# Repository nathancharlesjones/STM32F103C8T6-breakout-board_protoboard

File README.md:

# STM32F103C8T6 Breakout Board - Protoboard

Breakout board for the venerable STM32F103C8T6 (a.k.a. the "Blue Pill") intended to be assembled by JLC PCB. Includes a small prototyping area which is intended to resemble the layout of a standard half-sized breadboard. All of the pads on the breadboard are connected through just a single trace on the bottom of the PCB. This allows some to be easily cut (using a hobby knife or small cutting tool such as a Dremel), which could allow for a slightly denser layout of some circuits.

For more information about this PCB and how to order one, visit [this Git repository](https://github.com/nathancharlesjones/STM32F103C8T6-breakout-board).

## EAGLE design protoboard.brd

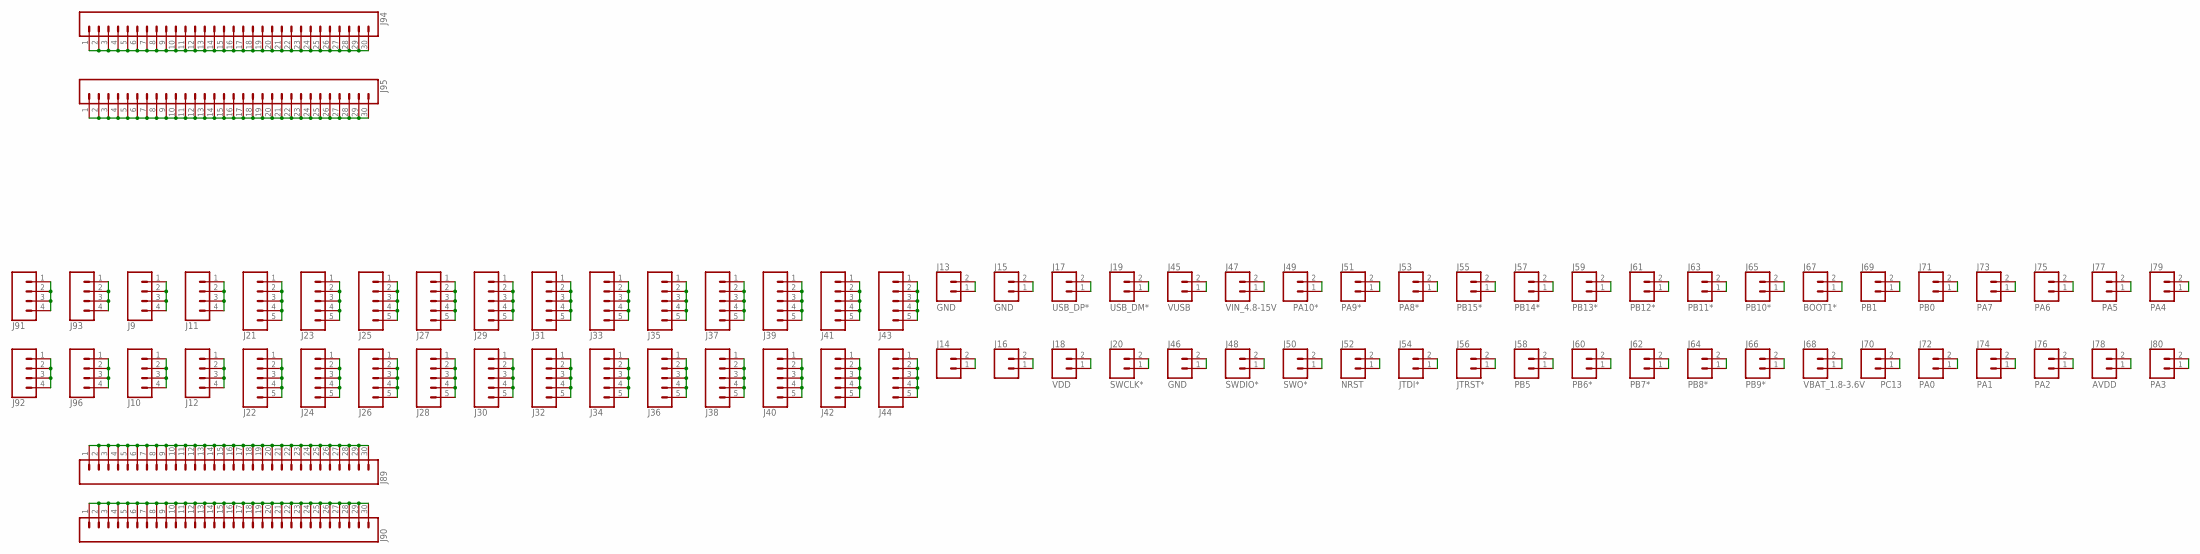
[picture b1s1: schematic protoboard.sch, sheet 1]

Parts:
J9, J10, J11, J12, J91, J92, J93, J96: CONN_041X04_NO_SILK; 1X04_NO_SILK
J13, J14, J15, J16, J17, J18, J19, J20, J45, J46, J47, J48, J49, J50, J51, J52, J53, J54, J55, J56, J57, J58, J59, J60, J61, J62, J63, J64, J65, J66, J67, J68, J69, J70, J71, J72, J73, J74, J75, J76, J77, J78, J79, J80: CONN_021X02_NO_SILK; 1X02_NO_SILK
J21, J22, J23, J24, J25, J26, J27, J28, J29, J30, J31, J32, J33, J34, J35, J36, J37, J38, J39, J40, J41, J42, J43, J44: CONN_05NO_SILK; 1X05_NO_SILK
J89, J90, J94, J95: CONN_30NO_SILK; 1X30_NO_SILK

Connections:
AVDD: J78.1, J78.2; also elsewhere on the board
BOOT1*: J67.1, J67.2; also elsewhere on the board
GND: J13.1, J13.2, J15.1, J15.2, J46.1, J46.2; also elsewhere on the board
JTDI*: J54.1, J54.2; also elsewhere on the board
JTRST*: J56.1, J56.2; also elsewhere on the board
unnamed: J90.1, J90.2, J90.3, J90.4, J90.5, J90.6, J90.7, J90.8, J90.9, J90.10, J90.11, J90.12, J90.13, J90.14, J90.15, J90.16, J90.17, J90.18, J90.19, J90.20, J90.21, J90.22, J90.23, J90.24, J90.25, J90.26, J90.27, J90.28, J90.29, J90.30
unnamed: J89.1, J89.2, J89.3, J89.4, J89.5, J89.6, J89.7, J89.8, J89.9, J89.10, J89.11, J89.12, J89.13, J89.14, J89.15, J89.16, J89.17, J89.18, J89.19, J89.20, J89.21, J89.22, J89.23, J89.24, J89.25, J89.26, J89.27, J89.28, J89.29, J89.30
unnamed: J95.1, J95.2, J95.3, J95.4, J95.5, J95.6, J95.7, J95.8, J95.9, J95.10, J95.11, J95.12, J95.13, J95.14, J95.15, J95.16, J95.17, J95.18, J95.19, J95.20, J95.21, J95.22, J95.23, J95.24, J95.25, J95.26, J95.27, J95.28, J95.29, J95.30
unnamed: J94.1, J94.2, J94.3, J94.4, J94.5, J94.6, J94.7, J94.8, J94.9, J94.10, J94.11, J94.12, J94.13, J94.14, J94.15, J94.16, J94.17, J94.18, J94.19, J94.20, J94.21, J94.22, J94.23, J94.24, J94.25, J94.26, J94.27, J94.28, J94.29, J94.30
unnamed: J92.1, J92.2, J92.3, J92.4
unnamed: J96.1, J96.2, J96.3, J96.4
unnamed: J10.1, J10.2, J10.3, J10.4
unnamed: J12.1, J12.2, J12.3, J12.4
unnamed: J22.1, J22.2, J22.3, J22.4, J22.5
unnamed: J24.1, J24.2, J24.3, J24.4, J24.5
unnamed: J26.1, J26.2, J26.3, J26.4, J26.5
unnamed: J28.1, J28.2, J28.3, J28.4, J28.5
unnamed: J30.1, J30.2, J30.3, J30.4, J30.5
unnamed: J32.1, J32.2, J32.3, J32.4, J32.5
unnamed: J34.1, J34.2, J34.3, J34.4, J34.5
unnamed: J36.1, J36.2, J36.3, J36.4, J36.5
unnamed: J38.1, J38.2, J38.3, J38.4, J38.5
unnamed: J40.1, J40.2, J40.3, J40.4, J40.5
unnamed: J42.1, J42.2, J42.3, J42.4, J42.5
unnamed: J44.1, J44.2, J44.3, J44.4, J44.5
unnamed: J14.1, J14.2
unnamed: J16.1, J16.2
unnamed: J91.1, J91.2, J91.3, J91.4
unnamed: J93.1, J93.2, J93.3, J93.4
unnamed: J9.1, J9.2, J9.3, J9.4
unnamed: J11.1, J11.2, J11.3, J11.4
unnamed: J21.1, J21.2, J21.3, J21.4, J21.5
unnamed: J23.1, J23.2, J23.3, J23.4, J23.5
unnamed: J25.1, J25.2, J25.3, J25.4, J25.5
unnamed: J27.1, J27.2, J27.3, J27.4, J27.5
unnamed: J29.1, J29.2, J29.3, J29.4, J29.5
unnamed: J31.1, J31.2, J31.3, J31.4, J31.5
unnamed: J33.1, J33.2, J33.3, J33.4, J33.5
unnamed: J35.1, J35.2, J35.3, J35.4, J35.5
unnamed: J37.1, J37.2, J37.3, J37.4, J37.5
unnamed: J39.1, J39.2, J39.3, J39.4, J39.5
unnamed: J41.1, J41.2, J41.3, J41.4, J41.5
unnamed: J43.1, J43.2, J43.3, J43.4, J43.5
NRST: J52.1, J52.2; also elsewhere on the board
PA0: J72.1, J72.2; also elsewhere on the board
PA1: J74.1, J74.2; also elsewhere on the board
PA2: J76.1, J76.2; also elsewhere on the board
PA3: J80.1, J80.2; also elsewhere on the board
PA4: J79.1, J79.2; also elsewhere on the board
PA5: J77.1, J77.2; also elsewhere on the board
PA6: J75.1, J75.2; also elsewhere on the board
PA7: J73.1, J73.2; also elsewhere on the board
PA8*: J53.1, J53.2; also elsewhere on the board
PA9*: J51.1, J51.2; also elsewhere on the board
PA10*: J49.1, J49.2; also elsewhere on the board
PB0: J71.1, J71.2; also elsewhere on the board
PB1: J69.1, J69.2; also elsewhere on the board
PB5: J58.1, J58.2; also elsewhere on the board
PB6*: J60.1, J60.2; also elsewhere on the board
PB7*: J62.1, J62.2; also elsewhere on the board
PB8*: J64.1, J64.2; also elsewhere on the board
PB9*: J66.1, J66.2; also elsewhere on the board
PB10*: J65.1, J65.2; also elsewhere on the board
PB11*: J63.1, J63.2; also elsewhere on the board
PB12*: J61.1, J61.2; also elsewhere on the board
PB13*: J59.1, J59.2; also elsewhere on the board
PB14*: J57.1, J57.2; also elsewhere on the board
PB15*: J55.1, J55.2; also elsewhere on the board
PC13: J70.1, J70.2; also elsewhere on the board
SWCLK*: J20.1, J20.2; also elsewhere on the board
SWDIO*: J48.1, J48.2; also elsewhere on the board
SWO*: J50.1, J50.2; also elsewhere on the board
USB_DM*: J19.1, J19.2; also elsewhere on the board
USB_DP*: J17.1, J17.2; also elsewhere on the board
VBAT_1.8-3.6V: J68.1, J68.2; also elsewhere on the board
VDD: J18.1, J18.2; also elsewhere on the board
VIN_4.8-15V: J47.1, J47.2; also elsewhere on the board
VUSB: J45.1, J45.2; also elsewhere on the board

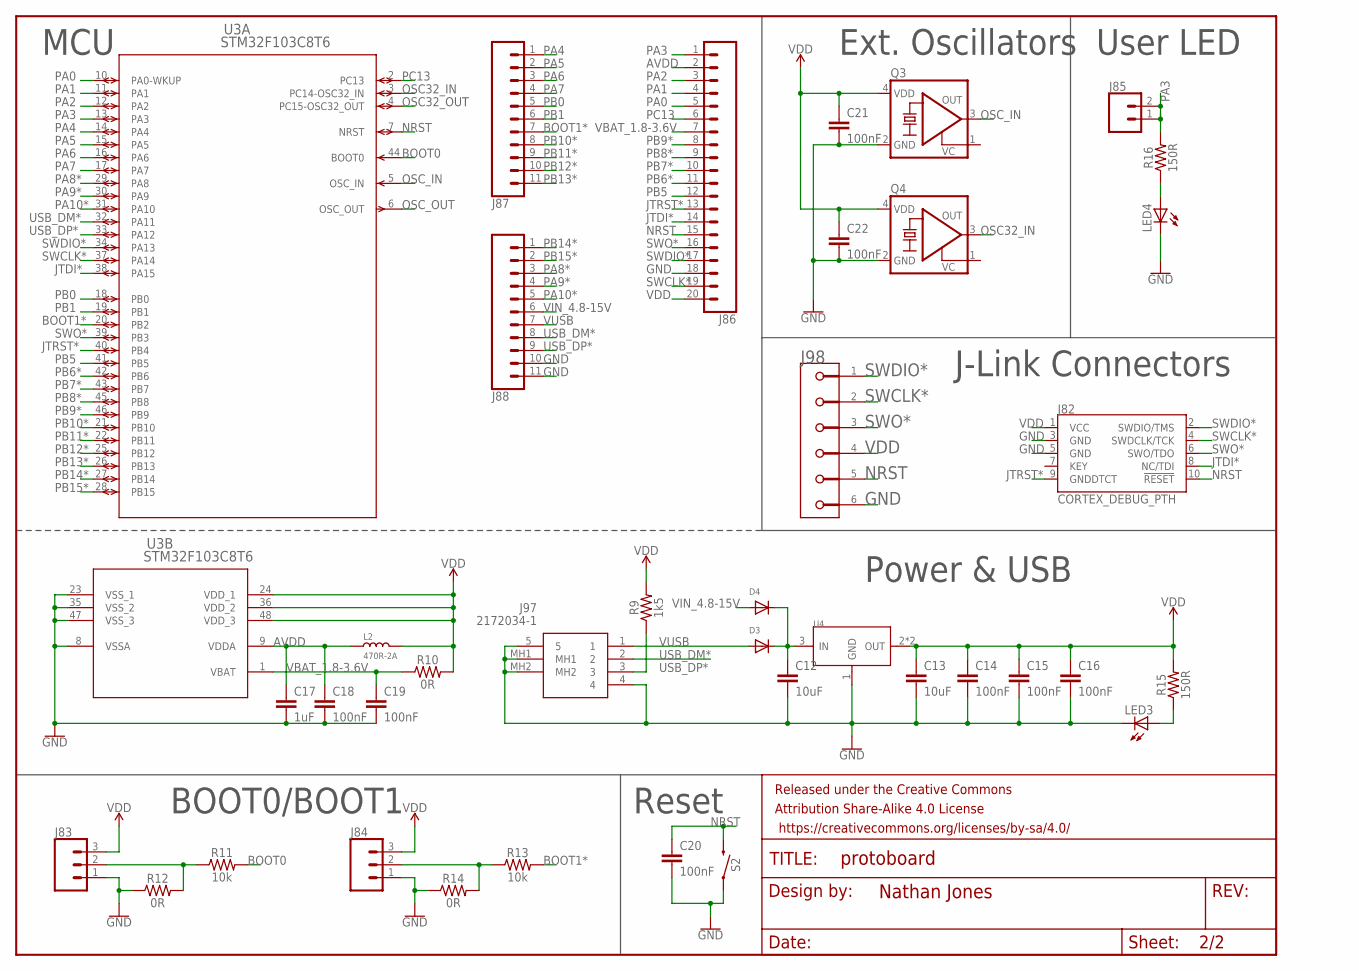
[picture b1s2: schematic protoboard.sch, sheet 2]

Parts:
C12, C13: 10uF; 0402-TIGHT; LCSC_PART C15525
C14, C15, C16, C18, C19, C20, C21, C22: 100nF; 0402-TIGHT; LCSC_PART C1525
C17: 1uF; 0402-TIGHT; LCSC_PART C52923
D3, D4: DIODESOD-123; SOD-123; LCSC_PART C8598
FRAME1: FRAME-LETTERNO_PACKAGE; DUMMY
J82: CORTEX_DEBUG_PTH; 2X5-PTH-1.27MM
J83, J84: CONN_031X03_NO_SILK; 1X03_NO_SILK
J85: CONN_021X02_NO_SILK; 1X02_NO_SILK
J86: CONN_20NOSILK; 1X20_NOSILK
J87, J88: CONN_111X11_NO_SILK; 1X11_NO_SILK
J97: 2172034-1; 21720341
J98: AVX_6-PIN_009159006061916_33MIL-GAP
L2: 470R-2A; L0805; LCSC_PART C1015
LED3: LEDCHIPLED_0603; CHIPLED_0603; LCSC_PART C72041
LED4: LEDCHIPLED_0603; CHIPLED_0603; LCSC_PART C72038
Q3: KXO-VCXO-CMOS_4; 3.2X2.5_KXO-84-TCXO; LCSC_PART C39097
Q4: KXO-VCXO-CMOS_4; 3.2X2.5_KXO-84-TCXO; LCSC_PART C387415
R9: 1k5; 0402; LCSC_PART C25867
R10, R12, R14: 0R; 0402; LCSC_PART C17168
R11, R13: 10k; 0402; LCSC_PART C25744
R15, R16: 150R; 0402; LCSC_PART C25082
S2: MOMENTARY-SWITCH-SPST-SMD-5.2-REDUNDANT; TACTILE_SWITCH_SMD_5.2MM; LCSC_PART C318884
U3: STM32F103C8T6; LQFP48-7X7MM; LCSC_PART C94046
U4: CJT1117-3.3-SOT223; SOT-223; LCSC_PART C6186

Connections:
AVDD: C17.1, C18.1, J86.2, L2.1, U3.9 (VDDA); also elsewhere on the board
BOOT0: R11.2, U3.44 (BOOT0)
BOOT1*: J87.7, R13.2, U3.20 (PB2); also elsewhere on the board
GND: C12.2, C13.2, C14.2, C15.2, C16.2, C17.2, C18.2, C19.2, C20.2, C21.2, C22.2, J82.3 (GND), J82.5 (GND), J83.1, J84.1, J86.18, J88.10, J88.11, J97.4, J97.5, J97.MH1, J97.MH2, J98.6, LED3.C, LED4.C, Q3.2 (GND), Q4.2 (GND), R12.1, R14.1, S2.1, S2.2 (1), U3.8 (VSSA), U3.23 (VSS_1), U3.35 (VSS_2), U3.47 (VSS_3), U4.1 (GND); also elsewhere on the board
JTDI*: J82.8 (NC/TDI), J86.14, U3.38 (PA15); also elsewhere on the board
JTRST*: J82.9 (GNDDTCT), J86.13, U3.40 (PB4); also elsewhere on the board
unnamed: J83.2, R11.1, R12.2
unnamed: J84.2, R13.1, R14.2
unnamed: LED4.A, R16.1
unnamed: LED3.A, R15.1
NRST: C20.1, J82.10 (!RESET), J86.15, J98.5, S2.3 (2), S2.4 (2), U3.7 (NRST); also elsewhere on the board
OSC32_IN: Q4.3 (OUT), U3.3 (PC14-OSC32_IN)
OSC32_OUT: U3.4 (PC15-OSC32_OUT)
OSC_IN: Q3.3 (OUT), U3.5 (OSC_IN)
OSC_OUT: U3.6 (OSC_OUT)
PA0: J86.5, U3.10 (PA0-WKUP); also elsewhere on the board
PA1: J86.4, U3.11 (PA1); also elsewhere on the board
PA2: J86.3, U3.12 (PA2); also elsewhere on the board
PA3: J85.1, J85.2, J86.1, R16.2, U3.13 (PA3); also elsewhere on the board
PA4: J87.1, U3.14 (PA4); also elsewhere on the board
PA5: J87.2, U3.15 (PA5); also elsewhere on the board
PA6: J87.3, U3.16 (PA6); also elsewhere on the board
PA7: J87.4, U3.17 (PA7); also elsewhere on the board
PA8*: J88.3, U3.29 (PA8); also elsewhere on the board
PA9*: J88.4, U3.30 (PA9); also elsewhere on the board
PA10*: J88.5, U3.31 (PA10); also elsewhere on the board
PB0: J87.5, U3.18 (PB0); also elsewhere on the board
PB1: J87.6, U3.19 (PB1); also elsewhere on the board
PB5: J86.12, U3.41 (PB5); also elsewhere on the board
PB6*: J86.11, U3.42 (PB6); also elsewhere on the board
PB7*: J86.10, U3.43 (PB7); also elsewhere on the board
PB8*: J86.9, U3.45 (PB8); also elsewhere on the board
PB9*: J86.8, U3.46 (PB9); also elsewhere on the board
PB10*: J87.8, U3.21 (PB10); also elsewhere on the board
PB11*: J87.9, U3.22 (PB11); also elsewhere on the board
PB12*: J87.10, U3.25 (PB12); also elsewhere on the board
PB13*: J87.11, U3.26 (PB13); also elsewhere on the board
PB14*: J88.1, U3.27 (PB14); also elsewhere on the board
PB15*: J88.2, U3.28 (PB15); also elsewhere on the board
PC13: J86.6, U3.2 (PC13); also elsewhere on the board
SWCLK*: J82.4 (SWDCLK/TCK), J86.19, J98.2, U3.37 (PA14); also elsewhere on the board
SWDIO*: J82.2 (SWDIO/TMS), J86.17, J98.1, U3.34 (PA13); also elsewhere on the board
SWO*: J82.6 (SWO/TDO), J86.16, J98.3, U3.39 (PB3); also elsewhere on the board
USB_DM*: J88.8, J97.2, U3.32 (PA11); also elsewhere on the board
USB_DP*: J88.9, J97.3, R9.1, U3.33 (PA12); also elsewhere on the board
VBAT_1.8-3.6V: C19.1, J86.7, R10.1, U3.1 (VBAT); also elsewhere on the board
VDD: C13.1, C14.1, C15.1, C16.1, C21.1, C22.1, J82.1 (VCC), J83.3, J84.3, J86.20, J98.4, L2.2, Q3.4 (VDD), Q4.4 (VDD), R9.2, R10.2, R15.2, U3.24 (VDD_1), U3.36 (VDD_2), U3.48 (VDD_3), U4.2 (OUT), U4.TER (OUT); also elsewhere on the board
VIN2: C12.1, D3.C, D4.C, U4.3 (IN)
VIN_4.8-15V: D4.A, J88.6; also elsewhere on the board
VUSB: D3.A, J88.7, J97.1; also elsewhere on the board

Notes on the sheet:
MCU
Power & USB
Reset
BOOT0/BOOT1
Ext. Oscillators
User LED
J-Link Connectors

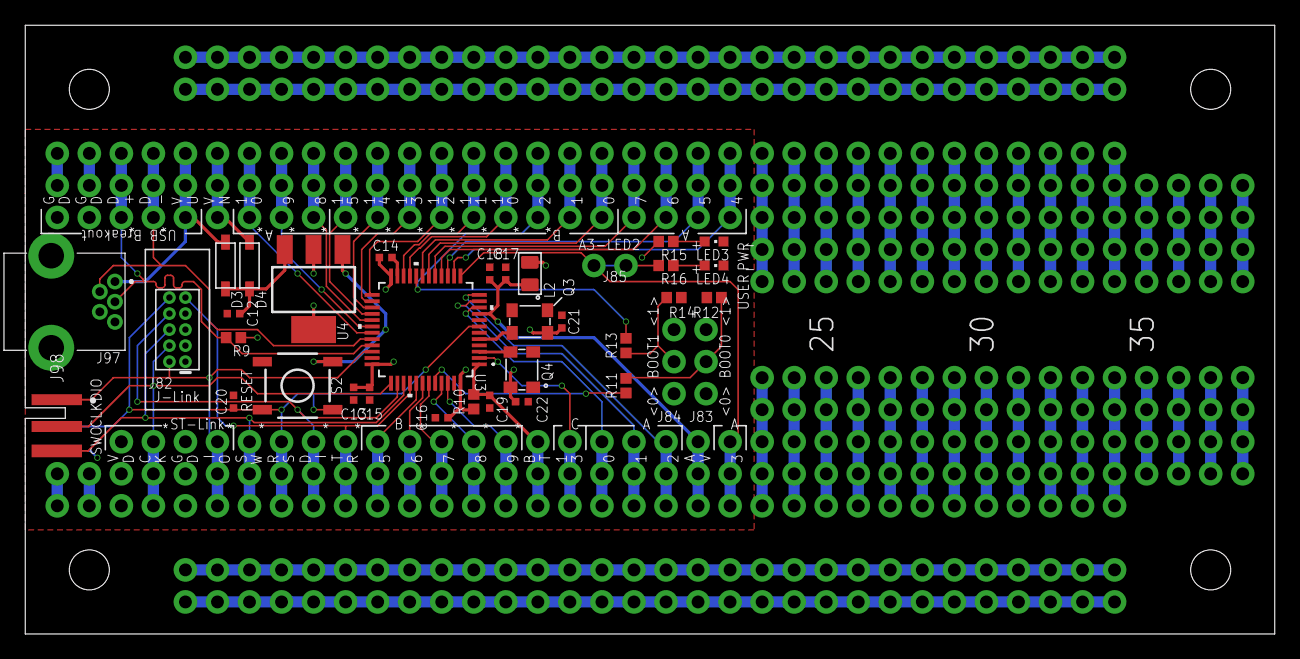
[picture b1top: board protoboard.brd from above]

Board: 2 copper layers, 99.1 x 48.3 mm, 119 parts (0 on the bottom side), 86 nets.

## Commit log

2021-01-02 Added files.
2021-01-02 Chaged file names.
2021-01-02 Removed temp files.
2021-01-05 Added screenshots.
2021-01-05 Updated screenshots.
2021-03-05 Updated design block. Switched USB from micro-B to mini-B. Updated Debug Edge library.
2021-03-05 Flipped horizontally protoboard_bottom.png

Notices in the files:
parts and their libraries:
SparkFun-Connectors: Licensing: Creative Commons ShareAlike 4.0 International - https://creativecommons.org/licenses/by-sa/4.0
crystal-geyer_V1_0: Copyright: Geyer-Electronic
COPYRIGHT: Copyright (C) 2018 Accelerated Designs. All rights reserved
